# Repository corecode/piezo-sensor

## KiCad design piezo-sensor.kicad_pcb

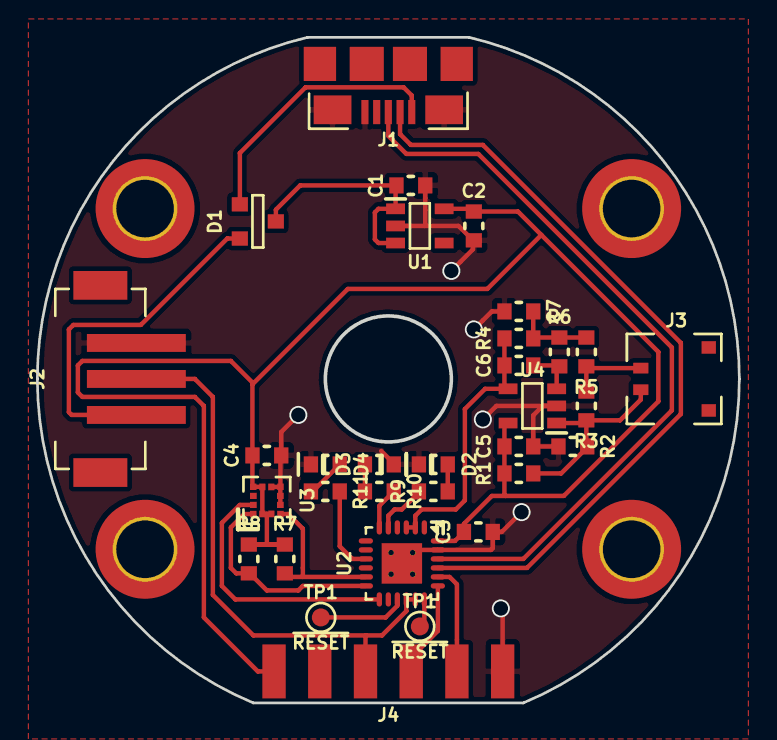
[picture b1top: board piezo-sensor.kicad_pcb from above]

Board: 2 copper layers, 39.0 x 36.9 mm, 36 parts (0 on the bottom side), 26 nets.

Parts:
C1, C2: 4.7u; SMD-1608
C3, C4, C5, C7: 0.1u; SMD-1608
C6: 4.7n; SMD-1608
D1: BAT54C; SOT-23
D2, D3: LED; SMD-1608-LED
D4: POWER; SMD-1608-LED
HOLE-M3, HOLE-M3#2, HOLE-M3#3, HOLE-M3#4: VAL**; HOLE-M3-COND
J1: USB-MICROB; USB-MICRO-B-FCI-10118192
J2: OUT; B3B-PH-SM4-TB
J3: PIEZO; JST-ACH-2
J4: DEBUG
R1, R2, R4, R7, R8, R9, R10, R11: 10k; SMD-1608
R3: 10M; SMD-1608
R5: 1k; SMD-1608
R6: 5.1k; SMD-1608
TP1, TP1#2: ~RESET; TESTPOINT-1.0
U1: MIC5205; SOT-23-5
U2: SAMD11D_QFN; qfn-24-4x4
U3: LIS2-LGA12; LGA12
U4: OP-AMP-SOT-23-5; SOT-23-5

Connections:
+3V3: C2.1, C3.1, C4.1, C5.1, J4.1, R1.1, R7.1, R8.1, U1.5, U2.24, U3.2, U3.3, U3.9, U3.10, U4.5
+5V: C1.1, D1.3, U1.1, U1.3
/DM: J1.2, U2.21
/DP: J1.3, U2.22
/INT: U2.13, U3.12
/LED1: R9.1, U2.5
/LED2: R10.1, U2.6
/LED3: R11.1, U2.9
/PIEZO: C6.1, R4.1, U2.2, U2.3, U4.4
/PIEZO_RAW: J3.2, R3.2, R5.1
/RXI: J2.2, J4.3, U2.16, U2.17
/SCL: R8.2, U2.12, U3.1
/SDA: R7.2, U2.11, U3.4
/SWCLK: J4.4, U2.19
/SWDIO: J4.5, U2.20
/TXO: J4.2, TP1.TP, U2.15
/~RESET: TP1#2.TP, U2.18
COM: C1.2, C2.2, C3.2, C4.2, C5.2, C7.2, D2.C, D3.C, D4.C, J1.5, J1.SHIE, J2.3, J4.6, R2.2, U1.2, U2.23, U2.FLAG, U3.5, U3.6, U3.7, U3.8, U4.2
unnamed: C6.2, R6.2, U4.3
unnamed: C7.1, R4.2, R5.2, R6.1
unnamed: D1.1, J1.1
unnamed: D1.2, J2.1
unnamed: D2.A, R9.2
unnamed: D3.A, R10.2
unnamed: D4.A, R11.2
unnamed: J3.1, R1.2, R2.1, R3.1, U4.1

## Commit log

2018-07-13 hotend z probe sensor board
